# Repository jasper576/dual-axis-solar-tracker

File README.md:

# dual-axis-solar-tracker
This is a Schoolproject, where I test whether or not a dual-axis-solar-panal is profitable

Manual of prototype 2 

system overview 

This solar tracker automatically follows the sun using for LDR light sensors and two servo motors. It also measures voltage, current, and power using an INA219 sensor and shows all the information on a small OLED screen 
navigating the screen 

Button 1: 
short press: starts a small measurement of 10 seconds
long press: puts both servos at 90 degrees 

Button 2: 
Short press: fluctuates between the servo positions screen, power screen, and the LDR sensor screen. 
long press: fluctuates between tracker modes.  

Manual of the monitor software
connecting the solar tracker. 
1.	Connect your solar tracker with the computer 
2.	Press rescan 
3.	Select the right port example: COM1 
4.	Press connect
5.	On the top right should stand; connected in green
starting measurements 
1.	Select a duration 
2.	Press start measurement 
collecting data
1.	After the measurement a popup should pop up
2.	Press yes and download the data.

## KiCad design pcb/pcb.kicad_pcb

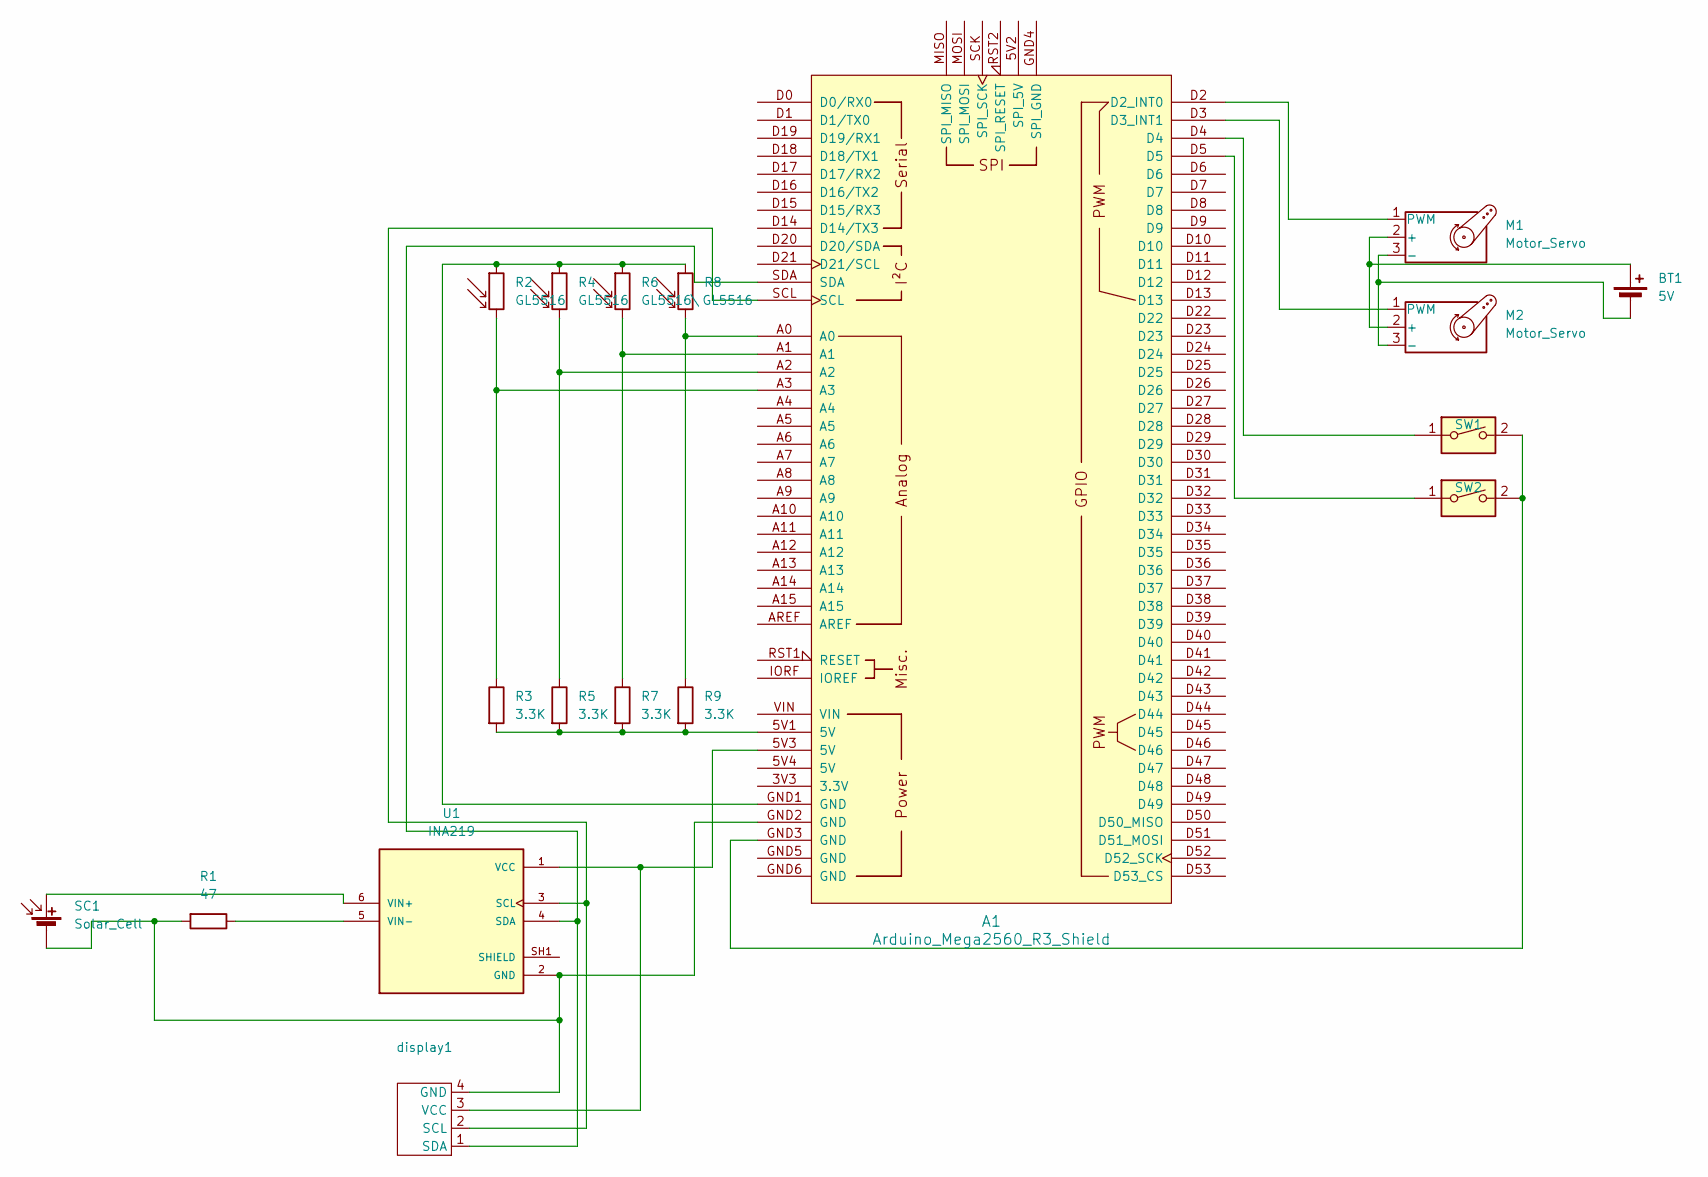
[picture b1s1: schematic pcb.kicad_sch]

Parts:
A1: Arduino_Mega2560_R3_Shield
BT1: 5V; PinHeader_1x02_P2.54mm_Horizontal
M1, M2: Motor_Servo; PinHeader_1x03_P2.54mm_Horizontal
R1: 47; R_Axial_DIN0207_L6.3mm_D2.5mm_P7.62mm_Horizontal
R2, R4, R8: GL5516; PinHeader_1x02_P2.54mm_Horizontal
R3, R5, R7, R9: 3.3K; R_Axial_DIN0207_L6.3mm_D2.5mm_P7.62mm_Horizontal
R6: GL5516\; PinHeader_1x02_P2.54mm_Horizontal
SC1: Solar_Cell; PinHeader_1x02_P2.54mm_Horizontal
SW1, SW2: SW_DIP_x01; PinHeader_1x02_P2.54mm_Horizontal
U1: INA219; MODULE_INA219; PARTREV C
display1: PinHeader_1x04_P2.54mm_Horizontal

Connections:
unnamed: A1.5V1 (5V), R3.2, R5.2, R7.2, R9.2
unnamed: A1.D2 (D2_INT0), M1.1 (PWM)
unnamed: A1.D3 (D3_INT1), M2.1 (PWM)
unnamed: A1.GND1 (GND), R2.1, R4.1, R6.1, R8.1
unnamed: A1.GND3 (GND), SW1.2, SW2.2
unnamed: A1.A0, R8.2, R9.1
unnamed: A1.A1, R6.2, R7.1
unnamed: A1.A2, R4.2, R5.1
unnamed: A1.A3, R2.2, R3.1
unnamed: A1.D4, SW1.1
unnamed: A1.D5, SW2.1
unnamed: BT1.1 (+), M1.2 (+), M2.2 (+)
unnamed: BT1.2 (-), M1.3 (-), M2.3 (-)
unnamed: R1.1, U1.5 (VIN-), U1.VIN-
unnamed: SC1.1 (+), U1.6 (VIN+), U1.VIN+
unnamed: A1.GND2 (GND), R1.2, SC1.2 (-), U1.2 (GND), display1.4 (GND)
unnamed: A1.SCL, U1.3 (SCL), display1.2 (SCL)
unnamed: A1.SDA, U1.4 (SDA), display1.1 (SDA)
unnamed: U1.SH1 (SHIELD), U1.SH2 (SHIELD), U1.SH3 (SHIELD), U1.SH4 (SHIELD)
unnamed: A1.5V3 (5V), U1.1 (VCC), display1.3 (VCC)

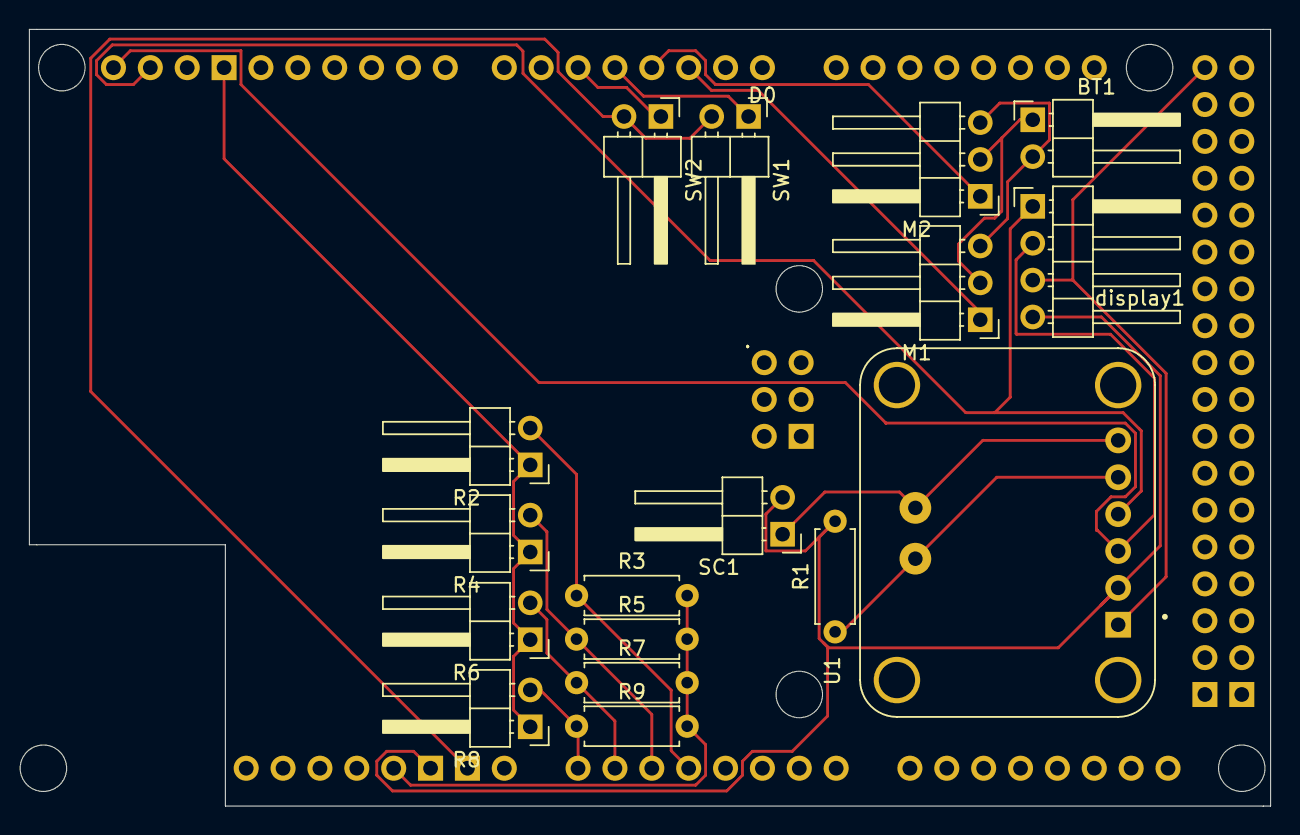
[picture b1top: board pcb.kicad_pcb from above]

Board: 2 copper layers, 85.5 x 53.5 mm, 18 parts (0 on the bottom side), 20 nets.

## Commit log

2026-04-22 3d printer files
2026-04-22 Freecad Files
2026-04-23 updated designs
    Arduino clearance
    Additional clearens was added beneath the arduino board to make clearens for the solder pins located on the underside. This allows the board to be mounted seculerly.
    Button Gap
    Gaps were introduced in the main compartment, that were previously forgotten.
    Display clearens
    Extra space was created aroud the display to accomondate the solder pins of the display to provide sufficient room for the display
2026-04-23 code prototype 1
    this is the code for the fisrt prototype
2026-05-25 test
